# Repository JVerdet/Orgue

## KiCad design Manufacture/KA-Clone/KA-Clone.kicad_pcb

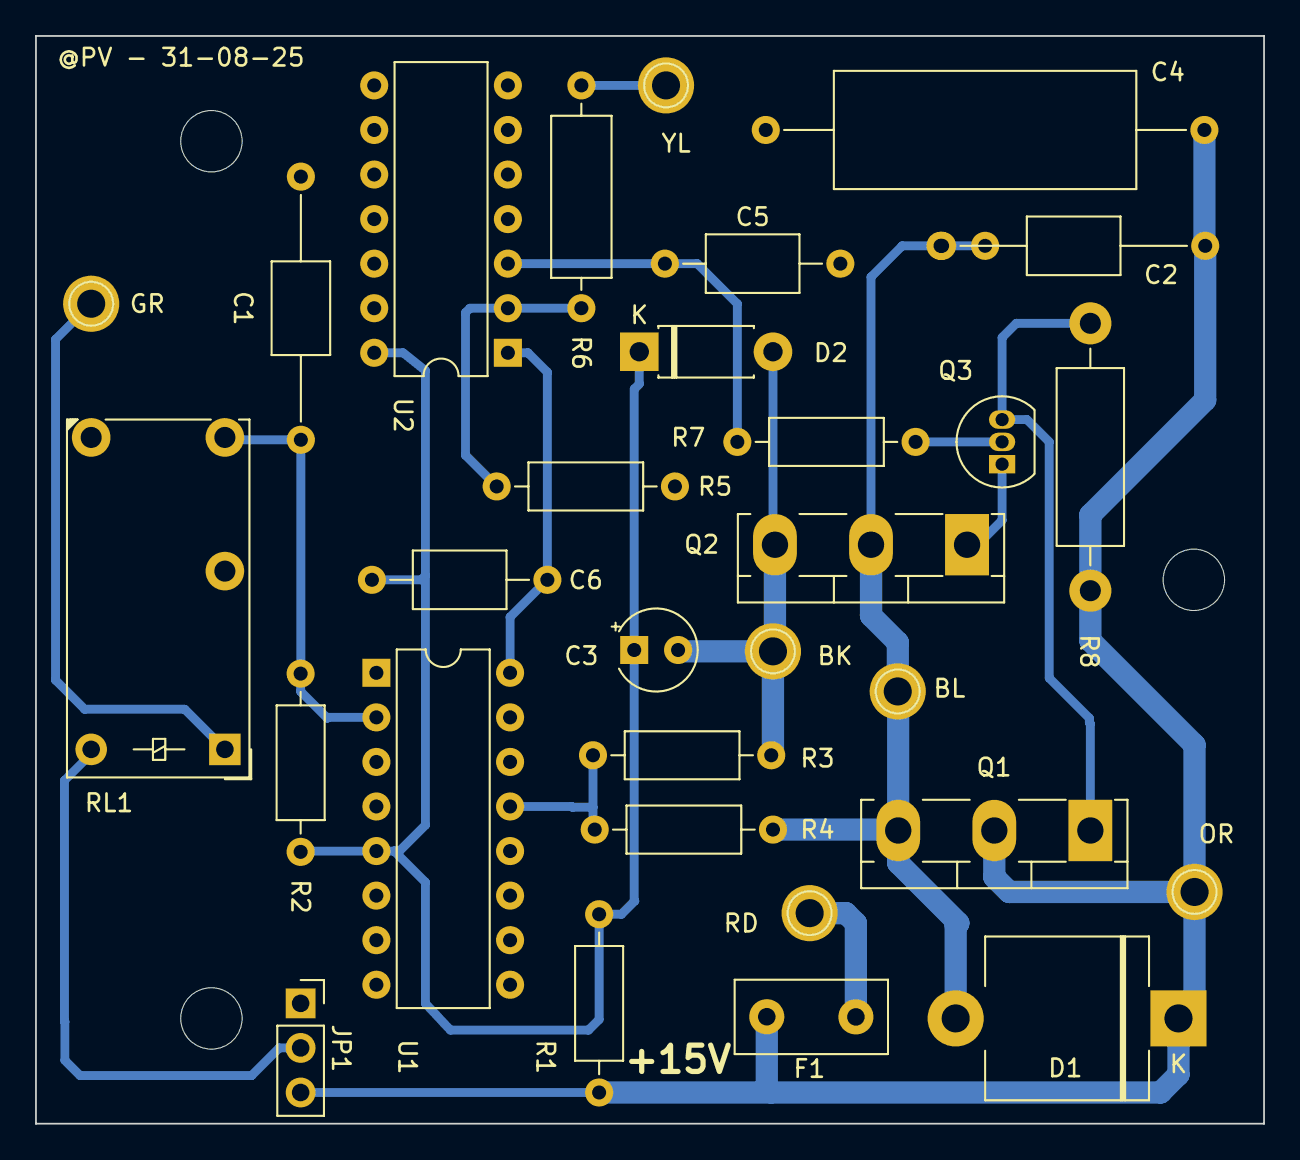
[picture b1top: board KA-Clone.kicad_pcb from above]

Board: 2 copper layers, 70.0 x 62.0 mm, 33 parts (0 on the bottom side), 16 nets.

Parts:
BK1: BLACK; Pin_D1.0mm_L10.0mm
BL1: BLUE; Pin_D1.0mm_L10.0mm
C1: 0.22µF; C_Axial_L5.1mm_D3.1mm_P15.00mm_Horizontal
C2: 0.1µF, 63V; C_Axial_L5.1mm_D3.1mm_P15.00mm_Horizontal
C3: 10µF, 16V; CP_Radial_Tantal_D4.5mm_P2.50mm
C4: 1µ, 250V; C_Axial_L17.0mm_D6.5mm_P25.00mm_Horizontal
C5: 0.1µF, 250V; C_Axial_L5.1mm_D3.1mm_P10.00mm_Horizontal
C6: 0.22µF; C_Axial_L5.1mm_D3.1mm_P10.00mm_Horizontal
D1: GI752; D_P600_R-6_P12.70mm_Horizontal
D2: BZX85C5V1; D_DO-41_SOD81_P7.62mm_Horizontal
F1: Polyfuse; Fuse_Littelfuse_395Series
GR1: GREEN; Pin_D1.0mm_L10.0mm
H1, H2, H3: MountingHole; MountingHole_3.5mm
JP1: Jumper_3_Bridged12; PinSocket_1x03_P2.54mm_Vertical
OR1: ORANGE; Pin_D1.0mm_L10.0mm
Q1, Q2: TIP141; TO-218-3_Vertical
Q3: 2N3904; TO-92_Inline
R1: 390, 1W; R_Axial_DIN0207_L6.3mm_D2.5mm_P10.16mm_Horizontal
R2, R3, R5: 1k; R_Axial_DIN0207_L6.3mm_D2.5mm_P10.16mm_Horizontal
R4: 2k4, 1/2W; R_Axial_DIN0207_L6.3mm_D2.5mm_P10.16mm_Horizontal
R6: 2k4, 1/2W; R_Axial_DIN0309_L9.0mm_D3.2mm_P12.70mm_Horizontal
R7: 470; R_Axial_DIN0207_L6.3mm_D2.5mm_P10.16mm_Horizontal
R8: 680, 1W; R_Axial_DIN0411_L9.9mm_D3.6mm_P15.24mm_Horizontal
RD1: RED; Pin_D1.0mm_L10.0mm
RL1: FINDER-32.21-x000; Relay_SPDT_Finder_32.21-x000
U1: 74LS75; DIP-16_W7.62mm
U2: 74LS86; DIP-14_W7.62mm
YL1: YELLOW; Pin_D1.0mm_L10.0mm

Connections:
+15V: C2.1, C4.1, D1.1 (K), F1.2, JP1.3 (B), OR1.1, Q1.2 (C), R1.1, R8.1
GND: BK1.1, C1.2, C3.2, C4.2, C5.2, D2.2 (A), JP1.1 (A), Q2.3 (E), R3.2, R5.2, RL1.11, U1.12 (GND), U2.7 (GND)
unnamed: BL1.1, C2.2, D1.2 (A), Q1.3 (E), Q2.2 (C), R4.1
unnamed: C5.1, R7.1, U2.3
unnamed: GR1.1, RL1.A1
unnamed: JP1.2 (C), RL1.A2
unnamed: Q1.1 (B), Q3.3 (C), R8.2
unnamed: Q2.1 (B), Q3.1 (E)
unnamed: Q3.2 (B), R7.2
unnamed: R5.1, R6.2, U2.2
unnamed: F1.1, RD1.1
unnamed: C1.1, R2.2, RL1.14, U1.2 (D0)
unnamed: R3.1, R4.2, U1.13 (E01)
unnamed: C6.2, U1.16 (Q0), U2.1
unnamed: R6.1, YL1.1
VCC: C3.1, C6.1, D2.1 (K), R1.2, R2.1, U1.5 (VCC), U2.14 (VCC)

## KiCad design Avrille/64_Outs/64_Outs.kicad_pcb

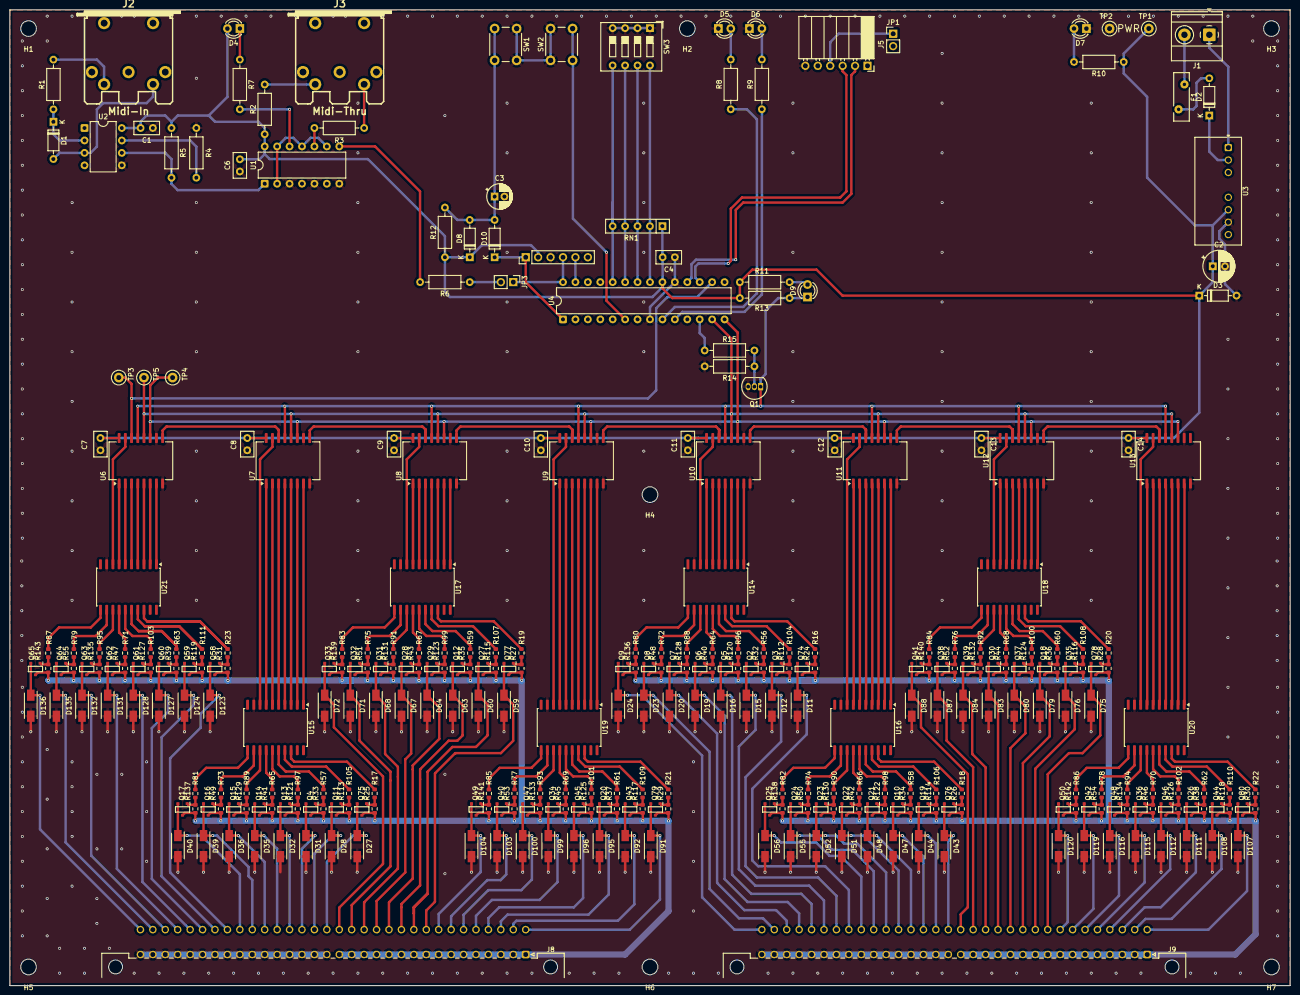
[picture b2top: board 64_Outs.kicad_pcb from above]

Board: 2 copper layers, 261.6 x 199.4 mm, 341 parts (0 on the bottom side), 308 nets.

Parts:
C1, C4, C6, C7, C8, C9, C10, C11, C12, C13, C14: 100n; C_Disc_D5.0mm_W2.5mm_P2.50mm
C2: 470µ; CP_Radial_D6.3mm_P2.50mm
C3: 10µ/16V; CP_Radial_D5.0mm_P2.00mm
D1, D8, D10: 1N4148; D_DO-35_SOD27_P7.62mm_Horizontal
D2: 1N4001; D_DO-35_SOD27_P7.62mm_Horizontal
D3: 1N4733; D_DO-35_SOD27_P7.62mm_Horizontal
D4: Midi_In; LED_D3.0mm
D5: Midi_Ack; LED_D3.0mm
D6: Run; LED_D3.0mm
D7: PWR; LED_D3.0mm
D9: ENABLE; LED_D3.0mm
D11, D12, D15, D16, D19, D20, D23, D24, D27, D28, D31, D32, D35, D36, D39, D40, D43, D44, D47, D48, D51, D52, D55, D56, D59, D60, D63, D64, D67, D68, D71, D72, D75, D76, D79, D80, D83, D84, D87, D88, D91, D92, D95, D96, D99, D100, D103, D104, D107, D108, D111, D112, D115, D116, D119, D120, D123, D124, D127, D128, D131, D132, D135, D136: MRA4004T3G; DIOM5226X220N
F1: Polyfuse; Fuse_Bourns_MF-RHT100
H1, H2, H3, H4, H5, H6, H7: MountingHole; MountingHole_3.2mm_M3
J1: POWER; TerminalBlock_Phoenix_MKDS-1,5-2-5.08_1x02_P5.08mm_Horizont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
J2: Midi-In; din-5
J3: Midi-Thru; din-5
J4: ICSP; PinHeader_1x06_P2.54mm_Vertical
J5: FT232; PinSocket_1x06_P2.54mm_Horizontal
J8, J9: DIN41612_02x32_AC; DIN41612_C_2x32_Male_Horizontal_THT
JP1: USB; PinHeader_1x02_P2.54mm_Vertical
JP3: Midi IN; PinHeader_1x02_P2.54mm_Vertical
Q1: BC337; TO-92_Inline
Q2, Q3, Q4, Q5, Q6, Q7, Q8, Q9, Q10, Q11, Q12, Q13, Q14, Q15, Q16, Q17, Q18, Q19, Q20, Q21, Q22, Q23, Q24, Q25, Q26, Q27, Q28, Q29, Q30, Q31, Q32, Q33, Q34, Q35, Q36, Q37, Q38, Q39, Q40, Q41, Q42, Q43, Q44, Q45, Q46, Q47, Q48, Q49, Q50, Q58, Q59, Q60, Q61, Q62, Q63, Q64, Q65, Q74, Q75, Q76, Q77, Q78, Q79, Q80: SSM3J351R; SOTFL95P240X88-3N
R1, R2, R3: 220; R_Axial_DIN0207_L6.3mm_D2.5mm_P10.16mm_Horizontal
R4, R5: 4,7k; R_Axial_DIN0207_L6.3mm_D2.5mm_P10.16mm_Horizontal
R6: 100; R_Axial_DIN0207_L6.3mm_D2.5mm_P10.16mm_Horizontal
R7, R8, R9, R10: 330; R_Axial_DIN0207_L6.3mm_D2.5mm_P10.16mm_Horizontal
R11: 1k; R_Axial_DIN0207_L6.3mm_D2.5mm_P10.16mm_Horizontal
R12, R13, R14, R15: 10k; R_Axial_DIN0207_L6.3mm_D2.5mm_P10.16mm_Horizontal
R16, R17, R18, R19, R20, R21, R22, R23, R56, R57, R58, R59, R60, R61, R62, R63, R64, R65, R66, R67, R68, R69, R70, R71, R72, R73, R74, R75, R76, R77, R78, R79, R80, R81, R82, R83, R84, R85, R86, R87, R88, R89, R90, R91, R92, R93, R94, R95, R96, R97, R98, R99, R100, R101, R102, R103, R104, R105, R106, R107, R108, R109, R110, R111: 10k; R_0603_1608Metric
R24, R25, R26, R27, R28, R29, R30, R31, R32, R33, R34, R35, R36, R37, R38, R39, R40, R41, R42, R43, R44, R45, R46, R47, R48, R49, R50, R51, R52, R53, R54, R55, R112, R113, R114, R115, R116, R117, R118, R119, R120, R121, R122, R123, R124, R125, R126, R127, R128, R129, R130, R131, R132, R133, R134, R135, R136, R137, R138, R139, R140, R141, R142, R143: 8,2k; R_0603_1608Metric
RN1: 10k; R_Array_SIP5
SW1: RESET; SW_PUSH_6mm
SW2: Prog; SW_PUSH_6mm
SW3: Channel; SW_DIP_SPSTx04_Slide_9.78x12.34mm_W7.62mm_P2.54mm
TP1: VCC; TestPoint_Loop_D2.50mm_Drill1.0mm
TP2: GND; TestPoint_Loop_D2.50mm_Drill1.0mm
TP3: DATA; TestPoint_Loop_D2.50mm_Drill1.0mm
TP4: CLOCK; TestPoint_Loop_D2.50mm_Drill1.0mm
TP5: LATCH; TestPoint_Loop_D2.50mm_Drill1.0mm
U1: 74HC14; DIP-14_W7.62mm
U2: 6N138; DIP-8_W7.62mm
U3: TMR 6-2411; Converter_DCDC_TRACO_TMR4-xxxxWI_THT
U4: PIC18F26K80; DIP-28_W7.62mm
U6, U7, U8, U9, U10, U11, U12, U13: 74HC595; SOIC-16W_7.5x12.8mm_P1.27mm
U14, U15, U16, U17, U18, U19, U20, U21: ULN2803A; SOIC-20W_7.5x12.8mm_P1.27mm

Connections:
/DATA_IN: TP3.1, U4.16 (RC5/SDO), U6.14 (SER)
/LAT: TP5.1, U4.13 (RC2/CCP1), U6.12 (RCLK), U7.12 (RCLK), U8.12 (RCLK), U9.12 (RCLK), U10.12 (RCLK), U11.12 (RCLK), U12.12 (RCLK), U13.12 (RCLK)
/LED_RUN: R9.1, U4.10 (OSC2/CLKO)
/Midi_Ack: R8.1, U4.9 (OSC1/CLKI)
/Midi_In: JP3.2 (B), R6.1
/Module_32/D1: U6.9 (QH'), U7.14 (SER)
/Module_32/D2: U7.9 (QH'), U8.14 (SER)
/Module_32/D3: U8.9 (QH'), U9.14 (SER)
/Module_32/DATA_OUT: U9.9 (QH'), U10.14 (SER)
/Module_32/O_00: D136.1 (K), J8.c32, Q65.2 (S)
/Module_32/O_01: D135.1 (K), J8.c31, Q64.2 (S)
/Module_32/O_02: D132.1 (K), J8.c30, Q63.2 (S)
/Module_32/O_03: D131.1 (K), J8.c29, Q62.2 (S)
/Module_32/O_04: D128.1 (K), J8.c28, Q61.2 (S)
/Module_32/O_05: D127.1 (K), J8.c27, Q60.2 (S)
/Module_32/O_06: D124.1 (K), J8.c26, Q59.2 (S)
/Module_32/O_07: D123.1 (K), J8.c25, Q58.2 (S)
/Module_32/O_08: D40.1 (K), J8.c24, Q17.2 (S)
/Module_32/O_09: D39.1 (K), J8.c23, Q16.2 (S)
/Module_32/O_10: D36.1 (K), J8.c22, Q15.2 (S)
/Module_32/O_11: D35.1 (K), J8.c21, Q14.2 (S)
/Module_32/O_12: D32.1 (K), J8.c20, Q13.2 (S)
/Module_32/O_13: D31.1 (K), J8.c19, Q4.2 (S)
/Module_32/O_14: D28.1 (K), J8.c18, Q11.2 (S)
/Module_32/O_15: D27.1 (K), J8.c17, Q75.2 (S)
/Module_32/O_16: D72.1 (K), J8.c16, Q33.2 (S)
/Module_32/O_17: D71.1 (K), J8.c15, Q32.2 (S)
/Module_32/O_18: D68.1 (K), J8.c14, Q31.2 (S)
/Module_32/O_19: D67.1 (K), J8.c13, Q28.2 (S)
/Module_32/O_20: D64.1 (K), J8.c12, Q29.2 (S)
/Module_32/O_21: D63.1 (K), J8.c11, Q12.2 (S)
/Module_32/O_22: D60.1 (K), J8.c10, Q27.2 (S)
/Module_32/O_23: D59.1 (K), J8.c9, Q77.2 (S)
/Module_32/O_24: D104.1 (K), J8.c8, Q49.2 (S)
/Module_32/O_25: D103.1 (K), J8.c7, Q40.2 (S)
/Module_32/O_26: D100.1 (K), J8.c6, Q47.2 (S)
/Module_32/O_27: D99.1 (K), J8.c5, Q34.2 (S)
/Module_32/O_28: D96.1 (K), J8.c4, Q45.2 (S)
/Module_32/O_29: D95.1 (K), J8.c3, Q20.2 (S)
/Module_32/O_30: D92.1 (K), J8.c2, Q43.2 (S)
/Module_32/O_31: D91.1 (K), J8.c1, Q79.2 (S)
/Module_32/Sorties_8/Cmd_1: R23.1, U21.18 (O1)
/Module_32/Sorties_8/Cmd_2: R111.1, U21.17 (O2)
/Module_32/Sorties_8/Cmd_3: R63.1, U21.16 (O3)
/Module_32/Sorties_8/Cmd_4: R103.1, U21.15 (O4)
/Module_32/Sorties_8/Cmd_5: R71.1, U21.14 (O5)
/Module_32/Sorties_8/Cmd_6: R95.1, U21.13 (O6)
/Module_32/Sorties_8/Cmd_7: R79.1, U21.12 (O7)
/Module_32/Sorties_8/Cmd_8: R87.1, U21.11 (O8)
/Module_32/Sorties_8/IN_1: U6.7 (QH), U21.1 (I1)
/Module_32/Sorties_8/IN_2: U6.6 (QG), U21.2 (I2)
/Module_32/Sorties_8/IN_3: U6.5 (QF), U21.3 (I3)
/Module_32/Sorties_8/IN_4: U6.4 (QE), U21.4 (I4)
/Module_32/Sorties_8/IN_5: U6.3 (QD), U21.5 (I5)
/Module_32/Sorties_8/IN_6: U6.2 (QC), U21.6 (I6)
/Module_32/Sorties_8/IN_7: U6.1 (QB), U21.7 (I7)
/Module_32/Sorties_8/IN_8: U6.15 (QA), U21.8 (I8)
/Module_32/Sorties_9/Cmd_1: R17.1, U15.18 (O1)
/Module_32/Sorties_9/Cmd_2: R105.1, U15.17 (O2)
/Module_32/Sorties_9/Cmd_3: R57.1, U15.16 (O3)
/Module_32/Sorties_9/Cmd_4: R97.1, U15.15 (O4)
/Module_32/Sorties_9/Cmd_5: R65.1, U15.14 (O5)
/Module_32/Sorties_9/Cmd_6: R89.1, U15.13 (O6)
/Module_32/Sorties_9/Cmd_7: R73.1, U15.12 (O7)
/Module_32/Sorties_9/Cmd_8: R81.1, U15.11 (O8)
/Module_32/Sorties_9/IN_1: U7.7 (QH), U15.1 (I1)
/Module_32/Sorties_9/IN_2: U7.6 (QG), U15.2 (I2)
/Module_32/Sorties_9/IN_3: U7.5 (QF), U15.3 (I3)
/Module_32/Sorties_9/IN_4: U7.4 (QE), U15.4 (I4)
/Module_32/Sorties_9/IN_5: U7.3 (QD), U15.5 (I5)
/Module_32/Sorties_9/IN_6: U7.2 (QC), U15.6 (I6)
/Module_32/Sorties_9/IN_7: U7.1 (QB), U15.7 (I7)
/Module_32/Sorties_9/IN_8: U7.15 (QA), U15.8 (I8)
/Module_32/Sorties_10/Cmd_1: R19.1, U17.18 (O1)
/Module_32/Sorties_10/Cmd_2: R107.1, U17.17 (O2)
/Module_32/Sorties_10/Cmd_3: R59.1, U17.16 (O3)
/Module_32/Sorties_10/Cmd_4: R99.1, U17.15 (O4)
/Module_32/Sorties_10/Cmd_5: R67.1, U17.14 (O5)
/Module_32/Sorties_10/Cmd_6: R91.1, U17.13 (O6)
/Module_32/Sorties_10/Cmd_7: R75.1, U17.12 (O7)
/Module_32/Sorties_10/Cmd_8: R83.1, U17.11 (O8)
/Module_32/Sorties_10/IN_1: U8.7 (QH), U17.1 (I1)
/Module_32/Sorties_10/IN_2: U8.6 (QG), U17.2 (I2)
/Module_32/Sorties_10/IN_3: U8.5 (QF), U17.3 (I3)
/Module_32/Sorties_10/IN_4: U8.4 (QE), U17.4 (I4)
/Module_32/Sorties_10/IN_5: U8.3 (QD), U17.5 (I5)
/Module_32/Sorties_10/IN_6: U8.2 (QC), U17.6 (I6)
/Module_32/Sorties_10/IN_7: U8.1 (QB), U17.7 (I7)
/Module_32/Sorties_10/IN_8: U8.15 (QA), U17.8 (I8)
/Module_32/Sorties_10/V_IN: J8.a1, J8.a2, J8.a3, J8.a4, J8.a5, J8.a6, J8.a7, J8.a8, J8.a9, J8.a10, J8.a11, J8.a12, J8.a13, J8.a14, J8.a15, J8.a16, Q4.3 (D), Q11.3 (D), Q12.3 (D), Q13.3 (D), Q14.3 (D), Q15.3 (D), Q16.3 (D), Q17.3 (D), Q20.3 (D), Q27.3 (D), Q28.3 (D), Q29.3 (D), Q31.3 (D), Q32.3 (D), Q33.3 (D), Q34.3 (D), Q40.3 (D), Q43.3 (D), Q45.3 (D), Q47.3 (D), Q49.3 (D), Q58.3 (D), Q59.3 (D), Q60.3 (D), Q61.3 (D), Q62.3 (D), Q63.3 (D), Q64.3 (D), Q65.3 (D), Q75.3 (D), Q77.3 (D), Q79.3 (D), R25.1, R27.1, R29.1, R31.1, R33.1, R35.1, R37.1, R39.1, R41.1, R43.1, R45.1, R47.1, R49.1, R51.1, R53.1, R55.1, R113.1, R115.1, R117.1, R119.1, R121.1, R123.1, R125.1, R127.1, R129.1, R131.1, R133.1, R135.1, R137.1, R139.1, R141.1, R143.1
/Module_32/Sorties_11/Cmd_1: R21.1, U19.18 (O1)
/Module_32/Sorties_11/Cmd_2: R109.1, U19.17 (O2)
/Module_32/Sorties_11/Cmd_3: R61.1, U19.16 (O3)
/Module_32/Sorties_11/Cmd_4: R101.1, U19.15 (O4)
/Module_32/Sorties_11/Cmd_5: R69.1, U19.14 (O5)
/Module_32/Sorties_11/Cmd_6: R93.1, U19.13 (O6)
/Module_32/Sorties_11/Cmd_7: R77.1, U19.12 (O7)
/Module_32/Sorties_11/Cmd_8: R85.1, U19.11 (O8)
/Module_32/Sorties_11/IN_1: U9.7 (QH), U19.1 (I1)
/Module_32/Sorties_11/IN_2: U9.6 (QG), U19.2 (I2)
/Module_32/Sorties_11/IN_3: U9.5 (QF), U19.3 (I3)
/Module_32/Sorties_11/IN_4: U9.4 (QE), U19.4 (I4)
/Module_32/Sorties_11/IN_5: U9.3 (QD), U19.5 (I5)
/Module_32/Sorties_11/IN_6: U9.2 (QC), U19.6 (I6)
/Module_32/Sorties_11/IN_7: U9.1 (QB), U19.7 (I7)
/Module_32/Sorties_11/IN_8: U9.15 (QA), U19.8 (I8)
/Module_33/D1: U10.9 (QH'), U11.14 (SER)
/Module_33/D2: U11.9 (QH'), U12.14 (SER)
/Module_33/D3: U12.9 (QH'), U13.14 (SER)
/Module_33/O_00: D24.1 (K), J9.c32, Q9.2 (S)
/Module_33/O_01: D23.1 (K), J9.c31, Q8.2 (S)
/Module_33/O_02: D20.1 (K), J9.c30, Q7.2 (S)
/Module_33/O_03: D19.1 (K), J9.c29, Q6.2 (S)
/Module_33/O_04: D16.1 (K), J9.c28, Q5.2 (S)
/Module_33/O_05: D15.1 (K), J9.c27, Q2.2 (S)
/Module_33/O_06: D12.1 (K), J9.c26, Q3.2 (S)
/Module_33/O_07: D11.1 (K), J9.c25, Q74.2 (S)
/Module_33/O_08: D56.1 (K), J9.c24, Q25.2 (S)
/Module_33/O_09: D55.1 (K), J9.c23, Q24.2 (S)
/Module_33/O_10: D52.1 (K), J9.c22, Q23.2 (S)
/Module_33/O_11: D51.1 (K), J9.c21, Q22.2 (S)
/Module_33/O_12: D48.1 (K), J9.c20, Q21.2 (S)
/Module_33/O_13: D47.1 (K), J9.c19, Q10.2 (S)
/Module_33/O_14: D44.1 (K), J9.c18, Q19.2 (S)
/Module_33/O_15: D43.1 (K), J9.c17, Q76.2 (S)
/Module_33/O_16: D88.1 (K), J9.c16, Q41.2 (S)
/Module_33/O_17: D87.1 (K), J9.c15, Q38.2 (S)
/Module_33/O_18: D84.1 (K), J9.c14, Q39.2 (S)
/Module_33/O_19: D83.1 (K), J9.c13, Q30.2 (S)
/Module_33/O_20: D80.1 (K), J9.c12, Q37.2 (S)
/Module_33/O_21: D79.1 (K), J9.c11, Q18.2 (S)
/Module_33/O_22: D76.1 (K), J9.c10, Q35.2 (S)
/Module_33/O_23: D75.1 (K), J9.c9, Q78.2 (S)
/Module_33/O_24: D120.1 (K), J9.c8, Q50.2 (S)
/Module_33/O_25: D119.1 (K), J9.c7, Q42.2 (S)
/Module_33/O_26: D116.1 (K), J9.c6, Q48.2 (S)
/Module_33/O_27: D115.1 (K), J9.c5, Q36.2 (S)
/Module_33/O_28: D112.1 (K), J9.c4, Q46.2 (S)
/Module_33/O_29: D111.1 (K), J9.c3, Q26.2 (S)
/Module_33/O_30: D108.1 (K), J9.c2, Q44.2 (S)
/Module_33/O_31: D107.1 (K), J9.c1, Q80.2 (S)
/Module_33/Sorties_8/Cmd_1: R16.1, U14.18 (O1)
/Module_33/Sorties_8/Cmd_2: R104.1, U14.17 (O2)
/Module_33/Sorties_8/Cmd_3: R56.1, U14.16 (O3)
/Module_33/Sorties_8/Cmd_4: R96.1, U14.15 (O4)
/Module_33/Sorties_8/Cmd_5: R64.1, U14.14 (O5)
/Module_33/Sorties_8/Cmd_6: R88.1, U14.13 (O6)
/Module_33/Sorties_8/Cmd_7: R72.1, U14.12 (O7)
/Module_33/Sorties_8/Cmd_8: R80.1, U14.11 (O8)
/Module_33/Sorties_8/IN_1: U10.7 (QH), U14.1 (I1)
/Module_33/Sorties_8/IN_2: U10.6 (QG), U14.2 (I2)
/Module_33/Sorties_8/IN_3: U10.5 (QF), U14.3 (I3)
/Module_33/Sorties_8/IN_4: U10.4 (QE), U14.4 (I4)
/Module_33/Sorties_8/IN_5: U10.3 (QD), U14.5 (I5)
/Module_33/Sorties_8/IN_6: U10.2 (QC), U14.6 (I6)
/Module_33/Sorties_8/IN_7: U10.1 (QB), U14.7 (I7)
/Module_33/Sorties_8/IN_8: U10.15 (QA), U14.8 (I8)
/Module_33/Sorties_9/Cmd_1: R18.1, U16.18 (O1)
/Module_33/Sorties_9/Cmd_2: R106.1, U16.17 (O2)
/Module_33/Sorties_9/Cmd_3: R58.1, U16.16 (O3)
/Module_33/Sorties_9/Cmd_4: R98.1, U16.15 (O4)
/Module_33/Sorties_9/Cmd_5: R66.1, U16.14 (O5)
/Module_33/Sorties_9/Cmd_6: R90.1, U16.13 (O6)
/Module_33/Sorties_9/Cmd_7: R74.1, U16.12 (O7)
/Module_33/Sorties_9/Cmd_8: R82.1, U16.11 (O8)
/Module_33/Sorties_9/IN_1: U11.7 (QH), U16.1 (I1)
/Module_33/Sorties_9/IN_2: U11.6 (QG), U16.2 (I2)
/Module_33/Sorties_9/IN_3: U11.5 (QF), U16.3 (I3)
/Module_33/Sorties_9/IN_4: U11.4 (QE), U16.4 (I4)
/Module_33/Sorties_9/IN_5: U11.3 (QD), U16.5 (I5)
/Module_33/Sorties_9/IN_6: U11.2 (QC), U16.6 (I6)
/Module_33/Sorties_9/IN_7: U11.1 (QB), U16.7 (I7)
/Module_33/Sorties_9/IN_8: U11.15 (QA), U16.8 (I8)
/Module_33/Sorties_10/Cmd_1: R20.1, U18.18 (O1)
/Module_33/Sorties_10/Cmd_2: R108.1, U18.17 (O2)
/Module_33/Sorties_10/Cmd_3: R60.1, U18.16 (O3)
/Module_33/Sorties_10/Cmd_4: R100.1, U18.15 (O4)
/Module_33/Sorties_10/Cmd_5: R68.1, U18.14 (O5)
/Module_33/Sorties_10/Cmd_6: R92.1, U18.13 (O6)
/Module_33/Sorties_10/Cmd_7: R76.1, U18.12 (O7)
/Module_33/Sorties_10/Cmd_8: R84.1, U18.11 (O8)
/Module_33/Sorties_10/IN_1: U12.7 (QH), U18.1 (I1)
/Module_33/Sorties_10/IN_2: U12.6 (QG), U18.2 (I2)
/Module_33/Sorties_10/IN_3: U12.5 (QF), U18.3 (I3)
/Module_33/Sorties_10/IN_4: U12.4 (QE), U18.4 (I4)
/Module_33/Sorties_10/IN_5: U12.3 (QD), U18.5 (I5)
/Module_33/Sorties_10/IN_6: U12.2 (QC), U18.6 (I6)
/Module_33/Sorties_10/IN_7: U12.1 (QB), U18.7 (I7)
/Module_33/Sorties_10/IN_8: U12.15 (QA), U18.8 (I8)
/Module_33/Sorties_10/V_IN: J9.a1, J9.a2, J9.a3, J9.a4, J9.a5, J9.a6, J9.a7, J9.a8, J9.a9, J9.a10, J9.a11, J9.a12, J9.a13, J9.a14, J9.a15, J9.a16, Q2.3 (D), Q3.3 (D), Q5.3 (D), Q6.3 (D), Q7.3 (D), Q8.3 (D), Q9.3 (D), Q10.3 (D), Q18.3 (D), Q19.3 (D), Q21.3 (D), Q22.3 (D), Q23.3 (D), Q24.3 (D), Q25.3 (D), Q26.3 (D), Q30.3 (D), Q35.3 (D), Q36.3 (D), Q37.3 (D), Q38.3 (D), Q39.3 (D), Q41.3 (D), Q42.3 (D), Q44.3 (D), Q46.3 (D), Q48.3 (D), Q50.3 (D), Q74.3 (D), Q76.3 (D), Q78.3 (D), Q80.3 (D), R24.1, R26.1, R28.1, R30.1, R32.1, R34.1, R36.1, R38.1, R40.1, R42.1, R44.1, R46.1, R48.1, R50.1, R52.1, R54.1, R112.1, R114.1, R116.1, R118.1, R120.1, R122.1, R124.1, R126.1, R128.1, R130.1, R132.1, R134.1, R136.1, R138.1, R140.1, R142.1
/Module_33/Sorties_11/Cmd_1: R22.1, U20.18 (O1)
/Module_33/Sorties_11/Cmd_2: R110.1, U20.17 (O2)
/Module_33/Sorties_11/Cmd_3: R62.1, U20.16 (O3)
/Module_33/Sorties_11/Cmd_4: R102.1, U20.15 (O4)
/Module_33/Sorties_11/Cmd_5: R70.1, U20.14 (O5)
/Module_33/Sorties_11/Cmd_6: R94.1, U20.13 (O6)
/Module_33/Sorties_11/Cmd_7: R78.1, U20.12 (O7)
/Module_33/Sorties_11/Cmd_8: R86.1, U20.11 (O8)
/Module_33/Sorties_11/IN_1: U13.7 (QH), U20.1 (I1)
/Module_33/Sorties_11/IN_2: U13.6 (QG), U20.2 (I2)
/Module_33/Sorties_11/IN_3: U13.5 (QF), U20.3 (I3)
/Module_33/Sorties_11/IN_4: U13.4 (QE), U20.4 (I4)
/Module_33/Sorties_11/IN_5: U13.3 (QD), U20.5 (I5)
/Module_33/Sorties_11/IN_6: U13.2 (QC), U20.6 (I6)
/Module_33/Sorties_11/IN_7: U13.1 (QB), U20.7 (I7)
/Module_33/Sorties_11/IN_8: U13.15 (QA), U20.8 (I8)
/PGC: J4.5, U4.27 (PGC/RB6)
/PGD: J4.4, JP3.1 (A), U4.28 (PGD/RB7)
/RxD: J5.3, U4.17 (RC6/CK/TX)
/SCL: TP4.1, U4.14 (RC3/SCK/SCL), U6.11 (SRCLK), U7.11 (SRCLK), U8.11 (SRCLK), U9.11 (SRCLK), U10.11 (SRCLK), U11.11 (SRCLK), U12.11 (SRCLK), U13.11 (SRCLK)
/TxD: J5.2, U4.18 (RC7/DT/RX)
/~MCLR: D10.1 (K), J4.1, U4.1 (~MCLR/Vpp)
/~OE: D9.1 (K), Q1.1 (C), R13.2, U6.13 (~OE), U7.13 (~OE), U8.13 (~OE), U9.13 (~OE), U10.13 (~OE), U11.13 (~OE), U12.13 (~OE), U13.13 (~OE)
GND: C1.1, C2.2, C3.2, C4.1, C6.2, C7.2, C8.2, C9.2, C10.2, C11.2, C12.2, C13.2, C14.2, D3.2 (A), D5.1 (K), D6.1 (K), D7.1 (K), D11.2 (A), D12.2 (A), D15.2 (A), D16.2 (A), D19.2 (A), D20.2 (A), D23.2 (A), D24.2 (A), D27.2 (A), D28.2 (A), D31.2 (A), D32.2 (A), D35.2 (A), D36.2 (A), D39.2 (A), D40.2 (A), D43.2 (A), D44.2 (A), D47.2 (A), D48.2 (A), D51.2 (A), D52.2 (A), D55.2 (A), D56.2 (A), D59.2 (A), D60.2 (A), D63.2 (A), D64.2 (A), D67.2 (A), D68.2 (A), D71.2 (A), D72.2 (A), D75.2 (A), D76.2 (A), D79.2 (A), D80.2 (A), D83.2 (A), D84.2 (A), D87.2 (A), D88.2 (A), D91.2 (A), D92.2 (A), D95.2 (A), D96.2 (A), D99.2 (A), D100.2 (A), D103.2 (A), D104.2 (A), D107.2 (A), D108.2 (A), D111.2 (A), D112.2 (A), D115.2 (A), D116.2 (A), D119.2 (A), D120.2 (A), D123.2 (A), D124.2 (A), D127.2 (A), D128.2 (A), D131.2 (A), D132.2 (A), D135.2 (A), D136.2 (A), J4.3, J5.6, J8.a17, J8.a18, J8.a19, J8.a20, J8.a21, J8.a22, J8.a23, J8.a24, J8.a25, J8.a26, J8.a27, J8.a28, J8.a29, J8.a30, J8.a31, J8.a32, J9.a17, J9.a18, J9.a19, J9.a20, J9.a21, J9.a22, J9.a23, J9.a24, J9.a25, J9.a26, J9.a27, J9.a28, J9.a29, J9.a30, J9.a31, J9.a32, Q1.3 (E), R4.2, R14.2, SW1.1, SW2.1, SW3.1, SW3.2, SW3.3, SW3.4, TP2.1, U1.3, U1.5, U1.7 (GND), U2.5 (GND), U3.7 (-VOUT), U4.8 (VSS), U4.19 (VSS), U6.8 (GND), U6.10 (~SRCLR), U7.8 (GND), U7.10 (~SRCLR), U8.8 (GND), U8.10 (~SRCLR), U9.8 (GND), U9.10 (~SRCLR), U10.8 (GND), U10.10 (~SRCLR), U11.8 (GND), U11.10 (~SRCLR), U12.8 (GND), U12.10 (~SRCLR), U13.8 (GND), U13.10 (~SRCLR), U14.9 (GND), U15.9 (GND), U16.9 (GND), U17.9 (GND), U18.9 (GND), U19.9 (GND), U20.9 (GND), U21.9 (GND)
unnamed: D1.2 (A), J2.5, U2.3 (C2)
unnamed: D1.1 (K), R1.1, U2.2 (C1)
unnamed: D2.2 (A), F1.2
unnamed: D4.1 (K), R7.1
unnamed: D5.2 (A), R8.2
unnamed: D6.2 (A), R9.2
unnamed: D7.2 (A), R10.2
unnamed: D9.2 (A), R11.1
unnamed: C3.1, D8.2 (A), D10.2 (A), R12.2, SW1.2
unnamed: J1.1, U3.1 (-VIN)
unnamed: F1.1, J1.2
unnamed: J2.4, R1.2
unnamed: J3.4, R2.2
unnamed: J3.5, R3.2
unnamed: J5.4, JP1.1 (A)
unnamed: Q1.2 (B), R14.1, R15.1
unnamed: Q2.1 (G), R32.2, R56.2
unnamed: Q3.1 (G), R104.2, R112.2
unnamed: Q4.1 (G), R33.2, R57.2
unnamed: Q5.1 (G), R96.2, R120.2
unnamed: Q6.1 (G), R40.2, R64.2
unnamed: Q7.1 (G), R88.2, R128.2
unnamed: Q8.1 (G), R48.2, R72.2
unnamed: Q9.1 (G), R80.2, R136.2
unnamed: Q10.1 (G), R34.2, R58.2
unnamed: Q11.1 (G), R105.2, R113.2
unnamed: Q12.1 (G), R35.2, R59.2
unnamed: Q13.1 (G), R97.2, R121.2
unnamed: Q14.1 (G), R41.2, R65.2
unnamed: Q15.1 (G), R89.2, R129.2
unnamed: Q16.1 (G), R49.2, R73.2
unnamed: Q17.1 (G), R81.2, R137.2
unnamed: Q18.1 (G), R36.2, R60.2
unnamed: Q19.1 (G), R106.2, R114.2
unnamed: Q20.1 (G), R37.2, R61.2
unnamed: Q21.1 (G), R98.2, R122.2
unnamed: Q22.1 (G), R42.2, R66.2
unnamed: Q23.1 (G), R90.2, R130.2
unnamed: Q24.1 (G), R50.2, R74.2
unnamed: Q25.1 (G), R82.2, R138.2
unnamed: Q26.1 (G), R38.2, R62.2
unnamed: Q27.1 (G), R107.2, R115.2
unnamed: Q28.1 (G), R43.2, R67.2
unnamed: Q29.1 (G), R99.2, R123.2
unnamed: Q30.1 (G), R44.2, R68.2
unnamed: Q31.1 (G), R91.2, R131.2
unnamed: Q32.1 (G), R51.2, R75.2
unnamed: Q33.1 (G), R83.2, R139.2
unnamed: Q34.1 (G), R45.2, R69.2
unnamed: Q35.1 (G), R108.2, R116.2
unnamed: Q36.1 (G), R46.2, R70.2
unnamed: Q37.1 (G), R100.2, R124.2
unnamed: Q38.1 (G), R52.2, R76.2
unnamed: Q39.1 (G), R92.2, R132.2
unnamed: Q40.1 (G), R53.2, R77.2
unnamed: Q41.1 (G), R84.2, R140.2
unnamed: Q42.1 (G), R54.2, R78.2
unnamed: Q43.1 (G), R109.2, R117.2
unnamed: Q44.1 (G), R110.2, R118.2
unnamed: Q45.1 (G), R101.2, R125.2
unnamed: Q46.1 (G), R102.2, R126.2
unnamed: Q47.1 (G), R93.2, R133.2
unnamed: Q48.1 (G), R94.2, R134.2
unnamed: Q49.1 (G), R85.2, R141.2
unnamed: Q50.1 (G), R86.2, R142.2
unnamed: Q58.1 (G), R23.2, R31.2
unnamed: Q59.1 (G), R111.2, R119.2
unnamed: Q60.1 (G), R39.2, R63.2
unnamed: Q61.1 (G), R103.2, R127.2
unnamed: Q62.1 (G), R47.2, R71.2
unnamed: Q63.1 (G), R95.2, R135.2
unnamed: Q64.1 (G), R55.2, R79.2
unnamed: Q65.1 (G), R87.2, R143.2
unnamed: Q74.1 (G), R16.2, R24.2
unnamed: Q75.1 (G), R17.2, R25.2
unnamed: Q76.1 (G), R18.2, R26.2
unnamed: Q77.1 (G), R19.2, R27.2
unnamed: Q78.1 (G), R20.2, R28.2
unnamed: Q79.1 (G), R21.2, R29.2
unnamed: Q80.1 (G), R22.2, R30.2
unnamed: R3.1, U1.10
unnamed: R6.2, U1.8
unnamed: R7.2, U1.12
unnamed: RN1.2 (R1), SW3.8, U4.21 (INT/RB0)
unnamed: RN1.3 (R2), SW3.7, U4.22 (RB1)
unnamed: RN1.4 (R3), SW3.6, U4.23 (RB2)
unnamed: RN1.5 (R4), SW3.5, U4.24 (PGM/RB3)
unnamed: U1.2, U1.9, U1.11, U1.13
unnamed: R4.1, U2.7 (VO1)
unnamed: R5.2, U1.1, U2.6 (VO2)
unnamed: R15.2, U4.12 (RC1/T1OSI/CCP2)
unnamed: SW2.2, U4.6 (T0CKI/RA4)
VCC: C1.2, C2.1, C4.2, C6.1, C7.1, C8.1, C9.1, C10.1, C11.1, C12.1, C13.1, C14.1, D3.1 (K), D4.2 (A), D8.1 (K), J4.2, R2.1, R5.1, R10.1, R11.2, R12.1, R13.1, RN1.1 (common), TP1.1, U1.14 (VCC), U2.8 (VCC), U3.6 (+VOUT), U4.20 (VDD), U6.16 (VCC), U7.16 (VCC), U8.16 (VCC), U9.16 (VCC), U10.16 (VCC), U11.16 (VCC), U12.16 (VCC), U13.16 (VCC)
VEE: D2.1 (K), U3.2 (+VIN)

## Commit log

2025-10-30 Update to SMD Version
2025-10-30 reset
2025-10-30 V1 schematicss
2025-10-30 Layout for Review
2025-10-30 Add KA_Clone
2025-10-31 Reduction taille pcb
